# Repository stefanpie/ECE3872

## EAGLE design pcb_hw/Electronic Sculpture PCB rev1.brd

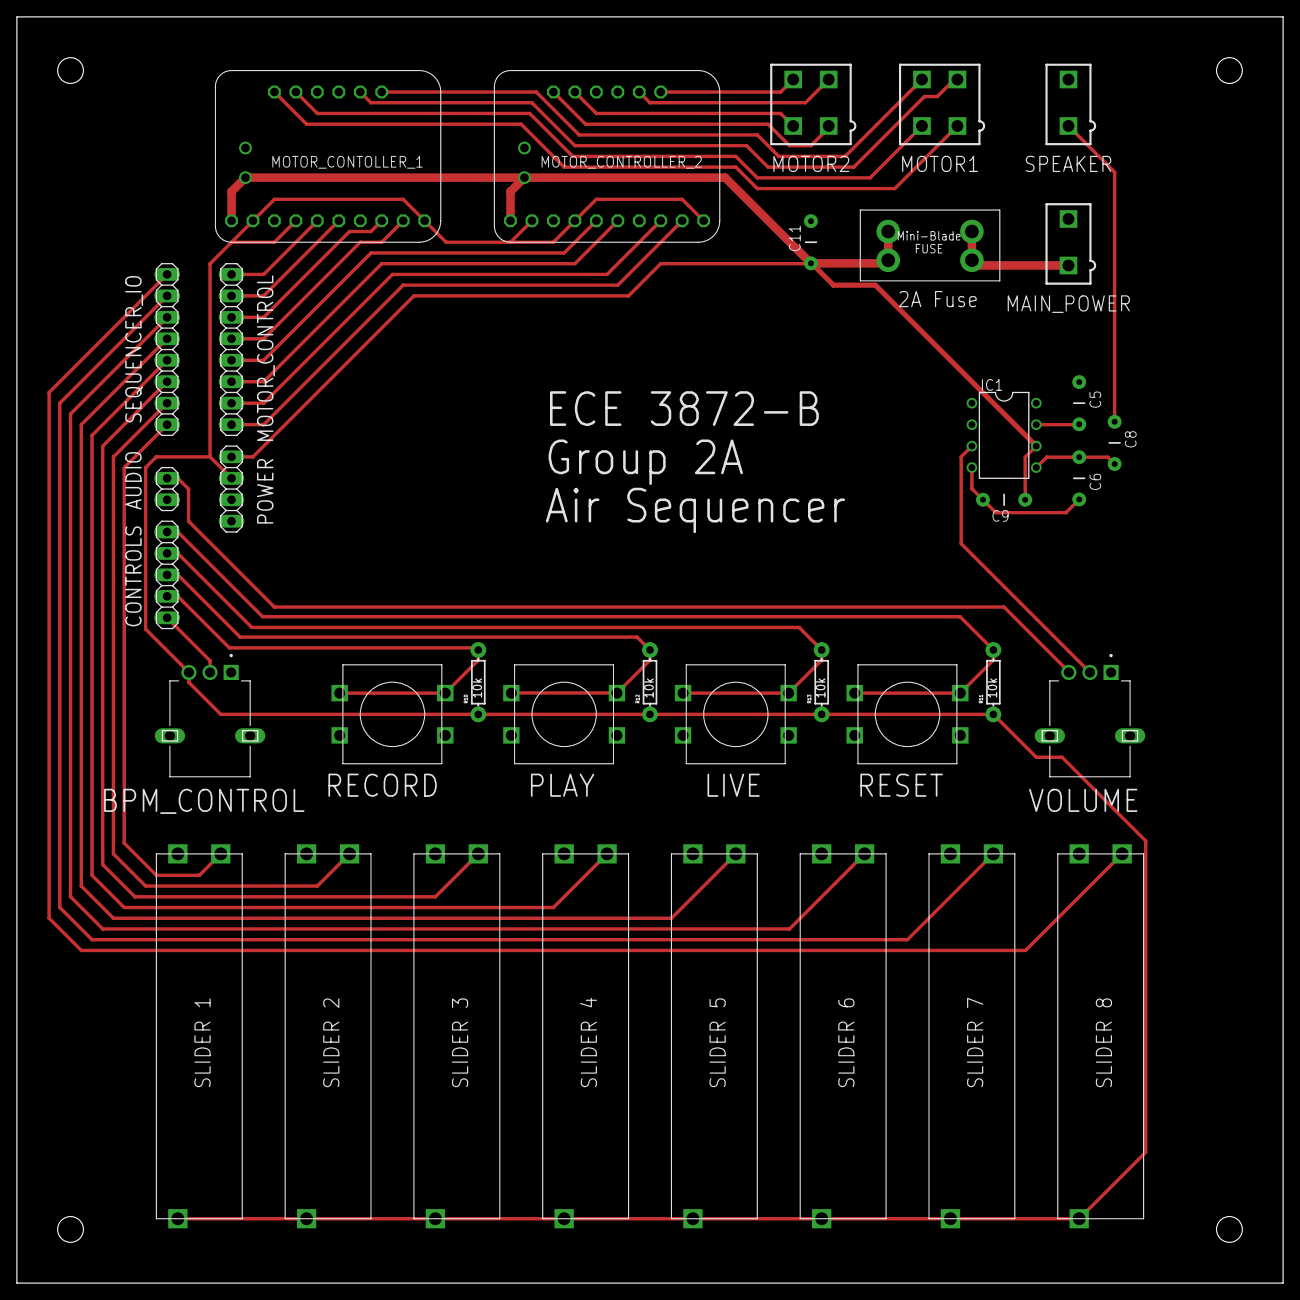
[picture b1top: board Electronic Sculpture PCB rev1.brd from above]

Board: 2 copper layers, 149.9 x 149.9 mm, 36 parts (0 on the bottom side), 38 nets.

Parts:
AUDIO: M02; 1X02
BPM_CONTROL: P0915N-QC20BR5K; TRIM_P0915N-QC20BR5K
C5, C9: 100uF; CAP-PTH-5MM
C6: 100nF; CAP-PTH-5MM
C8: 1000uF; CAP-PTH-5MM
C11: 10uF; CAP-PTH-5MM
CONTROLS: M05; 1X05
F1: 2A; MINI-BLADE_FUSE_HOLDER
IC1: LM386N-1; DIL08
LIVE: BIG_PUSHBUTTON
MAIN_POWER: CONNECTOR-2; MINIFIT_5566-2
MOTOR1, MOTOR2: CONNECTOR-4; MINIFIT_5566-4
MOTOR_CONTOLLER_1: TB6612_BREAKOUT
MOTOR_CONTROL: M08; 1X08
MOTOR_CONTROLLER_2: TB6612_BREAKOUT
PLAY: BIG_PUSHBUTTON
POWER: M04; 1X04
R10, R11, R12, R13: 10k; AXIAL-0.3
RECORD: BIG_PUSHBUTTON
RESET: BIG_PUSHBUTTON
SEQUENCER_IO: M08; 1X08
SLIDER_1, SLIDER_2, SLIDER_3, SLIDER_4, SLIDER_5, SLIDER_6, SLIDER_7, SLIDER_8: SLIDE_POT
SPEAKER: CONNECTOR-2; MINIFIT_5566-2
VOLUME: P0915N-QC20BR5K; TRIM_P0915N-QC20BR5K

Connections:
+5V: BPM_CONTROL.3, MOTOR_CONTOLLER_1.PWMA, MOTOR_CONTOLLER_1.PWMB, MOTOR_CONTOLLER_1.VCC, MOTOR_CONTROLLER_2.PWMA, MOTOR_CONTROLLER_2.PWMB, MOTOR_CONTROLLER_2.VCC, POWER.3, R10.P$1, R11.P$1, R12.P$1, R13.P$1, SLIDER_1.3, SLIDER_2.3, SLIDER_3.3, SLIDER_4.3, SLIDER_5.3, SLIDER_6.3, SLIDER_7.3, SLIDER_8.3
+12V: C9.1, C11.1, F1.R1, F1.R2, IC1.6, MOTOR_CONTOLLER_1.PWRIN1, MOTOR_CONTOLLER_1.PWRIN2, MOTOR_CONTROLLER_2.PWRIN1, MOTOR_CONTROLLER_2.PWRIN2, POWER.4
AUDIO_OUT: AUDIO.2, VOLUME.3
BPM_CONTROL: BPM_CONTROL.2, CONTROLS.1
CONTROL1_1: MOTOR_CONTOLLER_1.BIN2, MOTOR_CONTROL.1
CONTROL1_2: MOTOR_CONTOLLER_1.BIN1, MOTOR_CONTROL.2
CONTROL1_3: MOTOR_CONTOLLER_1.AIN1, MOTOR_CONTROL.3
CONTROL1_4: MOTOR_CONTOLLER_1.AIN2, MOTOR_CONTROL.4
CONTROL2_1: MOTOR_CONTROL.5, MOTOR_CONTROLLER_2.BIN2
CONTROL2_2: MOTOR_CONTROL.6, MOTOR_CONTROLLER_2.BIN1
CONTROL2_3: MOTOR_CONTROL.7, MOTOR_CONTROLLER_2.AIN1
CONTROL2_4: MOTOR_CONTROL.8, MOTOR_CONTROLLER_2.AIN2
GND: AUDIO.1, BPM_CONTROL.1, BPM_CONTROL.S1, BPM_CONTROL.S2, C5.2, C6.2, C9.2, C11.2, IC1.2, IC1.4, LIVE.1, LIVE.2, MAIN_POWER.2, MOTOR_CONTOLLER_1.GND1, MOTOR_CONTOLLER_1.GND2, MOTOR_CONTOLLER_1.GND3, MOTOR_CONTOLLER_1.GND4, MOTOR_CONTROLLER_2.GND1, MOTOR_CONTROLLER_2.GND2, MOTOR_CONTROLLER_2.GND3, MOTOR_CONTROLLER_2.GND4, PLAY.1, PLAY.2, POWER.1, POWER.2, RECORD.1, RECORD.2, RESET.1, RESET.2, SLIDER_1.1, SLIDER_2.1, SLIDER_3.1, SLIDER_4.1, SLIDER_5.1, SLIDER_6.1, SLIDER_7.1, SLIDER_8.1, SPEAKER.2, VOLUME.1, VOLUME.S1, VOLUME.S2
LIVE_BTN: CONTROLS.4, LIVE.3, LIVE.4, R13.P$2
MOTOR1_1: MOTOR1.1, MOTOR_CONTOLLER_1.MB1
MOTOR1_2: MOTOR1.2, MOTOR_CONTOLLER_1.MB2
MOTOR1_3: MOTOR1.3, MOTOR_CONTOLLER_1.MA2
MOTOR1_4: MOTOR1.4, MOTOR_CONTOLLER_1.MA1
MOTOR2_1: MOTOR2.1, MOTOR_CONTROLLER_2.MB1
MOTOR2_2: MOTOR2.2, MOTOR_CONTROLLER_2.MB2
MOTOR2_3: MOTOR2.3, MOTOR_CONTROLLER_2.MA2
MOTOR2_4: MOTOR2.4, MOTOR_CONTROLLER_2.MA1
unnamed: F1.L1, F1.L2, MAIN_POWER.1
unnamed: C5.1, IC1.7
unnamed: IC1.3, VOLUME.2
unnamed: C6.1, C8.1, IC1.5
PLAY_BTN: CONTROLS.3, PLAY.3, PLAY.4, R12.P$2
RECORD_BTN: CONTROLS.2, R10.P$2, RECORD.3, RECORD.4
RESET_BTN: CONTROLS.5, R11.P$2, RESET.3, RESET.4
SLIDER_1: SEQUENCER_IO.1, SLIDER_1.2
SLIDER_2: SEQUENCER_IO.2, SLIDER_2.2
SLIDER_3: SEQUENCER_IO.3, SLIDER_3.2
SLIDER_4: SEQUENCER_IO.4, SLIDER_4.2
SLIDER_5: SEQUENCER_IO.5, SLIDER_5.2
SLIDER_6: SEQUENCER_IO.6, SLIDER_6.2
SLIDER_7: SEQUENCER_IO.7, SLIDER_7.2
SLIDER_8: SEQUENCER_IO.8, SLIDER_8.2
SPEAKER_OUT: C8.2, SPEAKER.1

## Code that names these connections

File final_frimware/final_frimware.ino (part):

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double current_speed = 0;

char input;
#define RECORD_BTN  53
#define PLAY_BTN  51
#define LIVE_BTN  49
#define RESET_BTN  47



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  Serial.println("Live Sequence Function Demo");
  stepper_step.setSpeed(120);
  stepper_pitch.setSpeed(120);
  pinMode(RECORD_BTN, INPUT);
  pinMode(PLAY_BTN, INPUT);
  pinMode(LIVE_BTN, INPUT);
  pinMode(RESET_BTN, INPUT);
}

void loop()
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
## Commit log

2020-09-16 added simple simulation software template
2020-09-18 live sequence mode completed
2020-09-18 initial completion of simulation code
2020-09-18 added state machine stuff
2020-09-25 fixed bugs
2020-10-02 schematic for the PCB done-ish
2020-10-02 added control buttons to the schematic
2020-10-09 board design, gerbers
2020-11-06 added eagle for board design
2020-11-06 added final firmware for the box
2020-11-28 added prototyping code
